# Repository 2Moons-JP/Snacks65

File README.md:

# Snacks65
 When you need some snacks turn to the Snacks65

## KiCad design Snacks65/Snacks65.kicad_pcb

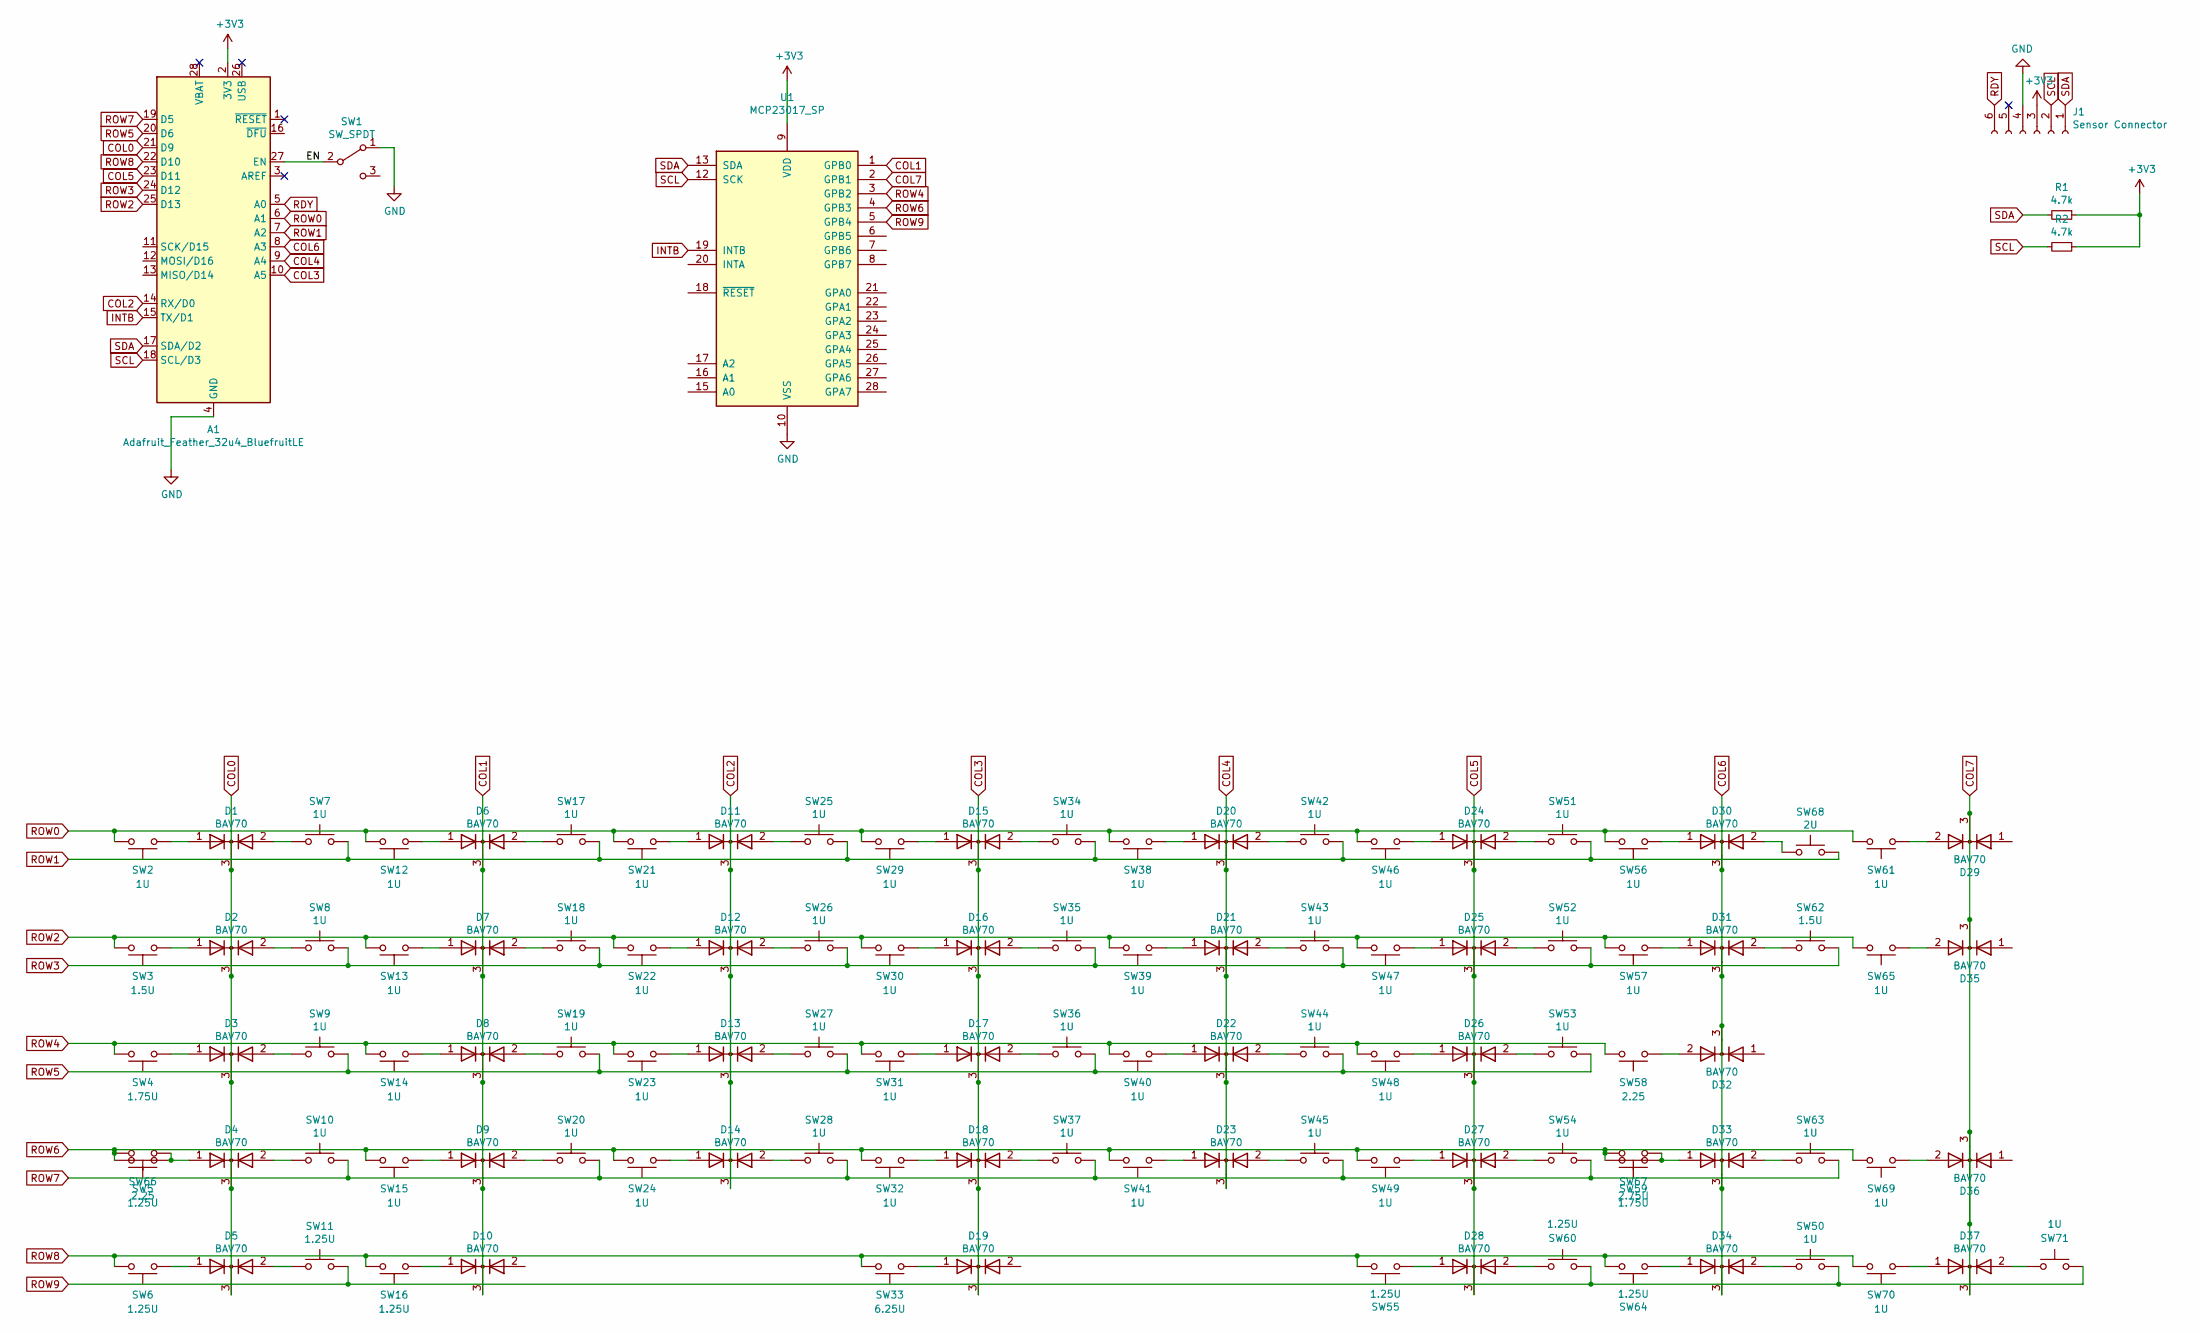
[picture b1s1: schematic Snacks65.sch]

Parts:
A1: Adafruit_Feather_32u4_BluefruitLE; Adafruit_Feather
D1, D2, D3, D4, D5, D6, D7, D8, D9, D10, D11, D12, D13, D14, D15, D16, D17, D18, D19, D20, D21, D22, D23, D24, D25, D26, D27, D28, D29, D30, D31, D32, D33, D34, D35, D36, D37: BAV70; SOT-23; Part# BAV70; LCSC Part# C68978
J1: Sensor Connector; Hirose_FH12-6S-0.5SH_1x06-1MP_P0.50mm_Horizontal; Part# FH12-6S-0.5SH(55); LCSC Part# C202118
R1, R2: 4.7k; R_0805_2012Metric; Part# 0805W8F4701T5E; LCSC Part# C17673
SW1: SW_SPDT; Slide_Switch_SPDT_ThroughHole; Part# SS-12D03-G4; LCSC Part# C698225
SW2, SW7, SW8, SW9, SW10, SW12, SW13, SW14, SW15, SW17, SW18, SW19, SW20, SW21, SW22, SW23, SW24, SW25, SW26, SW27, SW28, SW29, SW30, SW31, SW32, SW34, SW35, SW36, SW37, SW38, SW39, SW40, SW41, SW42, SW43, SW44, SW45, SW46, SW47, SW48, SW49, SW50, SW51, SW52, SW53, SW54, SW56, SW57, SW61, SW63, SW65, SW69, SW70, SW71: 1U; MX-1U-NoLED
SW3, SW62: 1.5U; MX-1.5U-NoLED
SW4, SW59: 1.75U; MX-1.75U-NoLED
SW5, SW6, SW11, SW16, SW55, SW60, SW64: 1.25U; MX-1.25U-NoLED
SW33: 6.25U; MX-6.25U-ReversedStabilizers-NoLED
SW58: 2.25; MX-2.25U-ReversedStabilizers-NoLED
SW66: 2.25; MX-2.25U-NoLED
SW67: 2.75U; MX-2.75U-ReversedStabilizers-NoLED
SW68: 2U; MX-2U-ReversedStabilizers-NoLED
U1: MCP23017_SP; DIP-28_W7.62mm

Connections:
+3V3: A1.2 (3V3), J1.3, R1.1, R2.1, U1.9 (VDD)
/EN: A1.27 (EN), SW1.2 (B)
COL0: A1.21 (D9), D1.3 (K), D2.3 (K), D3.3 (K), D4.3 (K), D5.3 (K)
COL1: D6.3 (K), D7.3 (K), D8.3 (K), D9.3 (K), D10.3 (K), U1.1 (GPB0)
COL2: A1.14 (RX/D0), D11.3 (K), D12.3 (K), D13.3 (K), D14.3 (K)
COL3: A1.10 (A5), D15.3 (K), D16.3 (K), D17.3 (K), D18.3 (K), D19.3 (K)
COL4: A1.9 (A4), D20.3 (K), D21.3 (K), D22.3 (K), D23.3 (K)
COL5: A1.23 (D11), D24.3 (K), D25.3 (K), D26.3 (K), D27.3 (K), D28.3 (K)
COL6: A1.8 (A3), D30.3 (K), D31.3 (K), D32.3 (K), D33.3 (K), D34.3 (K)
COL7: D29.3 (K), D35.3 (K), D36.3 (K), D37.3 (K), U1.2 (GPB1)
GND: A1.4 (GND), J1.4, SW1.1 (A), U1.10 (VSS)
INTB: A1.15 (TX/D1), U1.19 (INTB)
unnamed: D1.1 (A), SW2.1
unnamed: D1.2 (A), SW7.1
unnamed: D2.1 (A), SW3.1
unnamed: D2.2 (A), SW8.1
unnamed: D3.1 (A), SW4.1
unnamed: D3.2 (A), SW9.1
unnamed: D4.1 (A), SW5.1, SW66.1
unnamed: D4.2 (A), SW10.1
unnamed: D5.1 (A), SW6.1
unnamed: D5.2 (A), SW11.1
unnamed: D6.1 (A), SW12.1
unnamed: D6.2 (A), SW17.1
unnamed: D7.1 (A), SW13.1
unnamed: D7.2 (A), SW18.1
unnamed: D8.1 (A), SW14.1
unnamed: D8.2 (A), SW19.1
unnamed: D9.1 (A), SW15.1
unnamed: D9.2 (A), SW20.1
unnamed: D10.1 (A), SW16.1
unnamed: D11.1 (A), SW21.1
unnamed: D11.2 (A), SW25.1
unnamed: D12.1 (A), SW22.1
unnamed: D12.2 (A), SW26.1
unnamed: D13.1 (A), SW23.1
unnamed: D13.2 (A), SW27.1
unnamed: D14.1 (A), SW24.1
unnamed: D14.2 (A), SW28.1
unnamed: D15.1 (A), SW29.1
unnamed: D15.2 (A), SW34.1
unnamed: D16.1 (A), SW30.1
unnamed: D16.2 (A), SW35.1
unnamed: D17.1 (A), SW31.1
unnamed: D17.2 (A), SW36.1
unnamed: D18.1 (A), SW32.1
unnamed: D18.2 (A), SW37.1
unnamed: D19.1 (A), SW33.1
unnamed: D20.1 (A), SW38.1
unnamed: D20.2 (A), SW42.1
unnamed: D21.1 (A), SW39.1
unnamed: D21.2 (A), SW43.1
unnamed: D22.1 (A), SW40.1
unnamed: D22.2 (A), SW44.1
unnamed: D23.1 (A), SW41.1
unnamed: D23.2 (A), SW45.1
unnamed: D24.1 (A), SW46.1
unnamed: D24.2 (A), SW51.1
unnamed: D25.1 (A), SW47.1
unnamed: D25.2 (A), SW52.1
unnamed: D26.1 (A), SW48.1
unnamed: D26.2 (A), SW53.1
unnamed: D27.1 (A), SW49.1
unnamed: D27.2 (A), SW54.1
unnamed: D28.1 (A), SW55.1
unnamed: D28.2 (A), SW60.1
unnamed: D29.2 (A), SW61.1
unnamed: D30.1 (A), SW56.1
unnamed: D30.2 (A), SW68.1
unnamed: D31.1 (A), SW57.1
unnamed: D31.2 (A), SW62.1
unnamed: D32.2 (A), SW58.1
unnamed: D33.1 (A), SW59.1, SW67.1
unnamed: D33.2 (A), SW63.1
unnamed: D34.1 (A), SW64.1
unnamed: D34.2 (A), SW50.1
unnamed: D35.2 (A), SW65.1
unnamed: D36.2 (A), SW69.1
unnamed: D37.1 (A), SW70.1
unnamed: D37.2 (A), SW71.1
RDY: A1.5 (A0), J1.6
ROW0: A1.6 (A1), SW2.2, SW12.2, SW21.2, SW29.2, SW38.2, SW46.2, SW56.2, SW61.2
ROW1: A1.7 (A2), SW7.2, SW17.2, SW25.2, SW34.2, SW42.2, SW51.2, SW68.2
ROW2: A1.25 (D13), SW3.2, SW13.2, SW22.2, SW30.2, SW39.2, SW47.2, SW57.2, SW65.2
ROW3: A1.24 (D12), SW8.2, SW18.2, SW26.2, SW35.2, SW43.2, SW52.2, SW62.2
ROW4: SW4.2, SW14.2, SW23.2, SW31.2, SW40.2, SW48.2, SW58.2, U1.3 (GPB2)
ROW5: A1.20 (D6), SW9.2, SW19.2, SW27.2, SW36.2, SW44.2, SW53.2
ROW6: SW5.2, SW15.2, SW24.2, SW32.2, SW41.2, SW49.2, SW59.2, SW66.2, SW67.2, SW69.2, U1.4 (GPB3)
ROW7: A1.19 (D5), SW10.2, SW20.2, SW28.2, SW37.2, SW45.2, SW54.2, SW63.2
ROW8: A1.22 (D10), SW6.2, SW16.2, SW33.2, SW55.2, SW64.2, SW70.2
ROW9: SW11.2, SW50.2, SW60.2, SW71.2, U1.5 (GPB4)
SCL: A1.18 (SCL/D3), J1.2, R2.2, U1.12 (SCK)
SDA: A1.17 (SDA/D2), J1.1, R1.2, U1.13 (SDA)

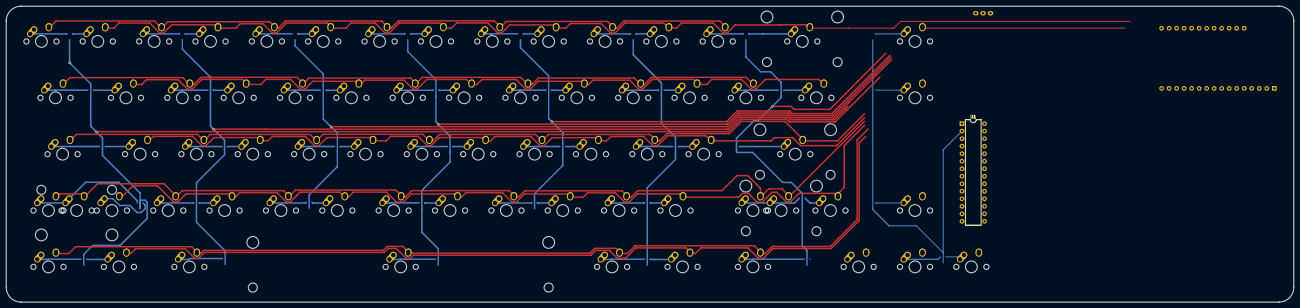
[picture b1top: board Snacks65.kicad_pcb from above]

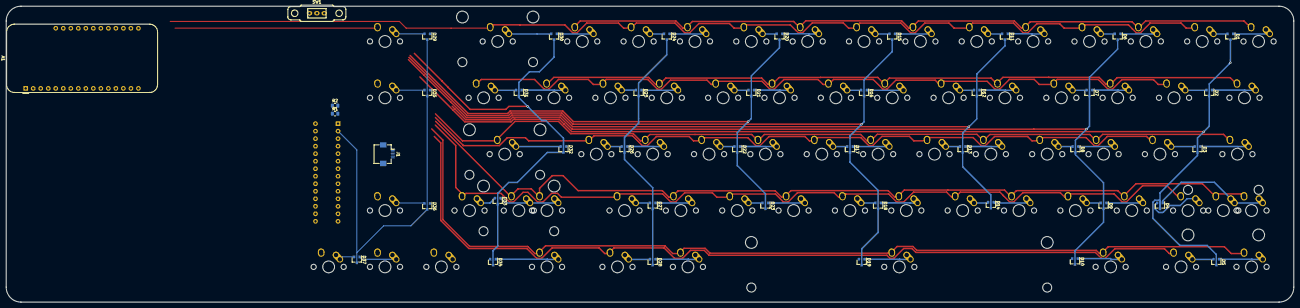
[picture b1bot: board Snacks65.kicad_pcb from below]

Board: 2 copper layers, 435.2 x 100.0 mm, 113 parts (42 on the bottom side), 93 nets.

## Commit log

2021-07-20 7/20/2021
2021-07-23 7/24
2021-07-26 7-27
2021-07-27 7/27
2021-08-29 8/29
